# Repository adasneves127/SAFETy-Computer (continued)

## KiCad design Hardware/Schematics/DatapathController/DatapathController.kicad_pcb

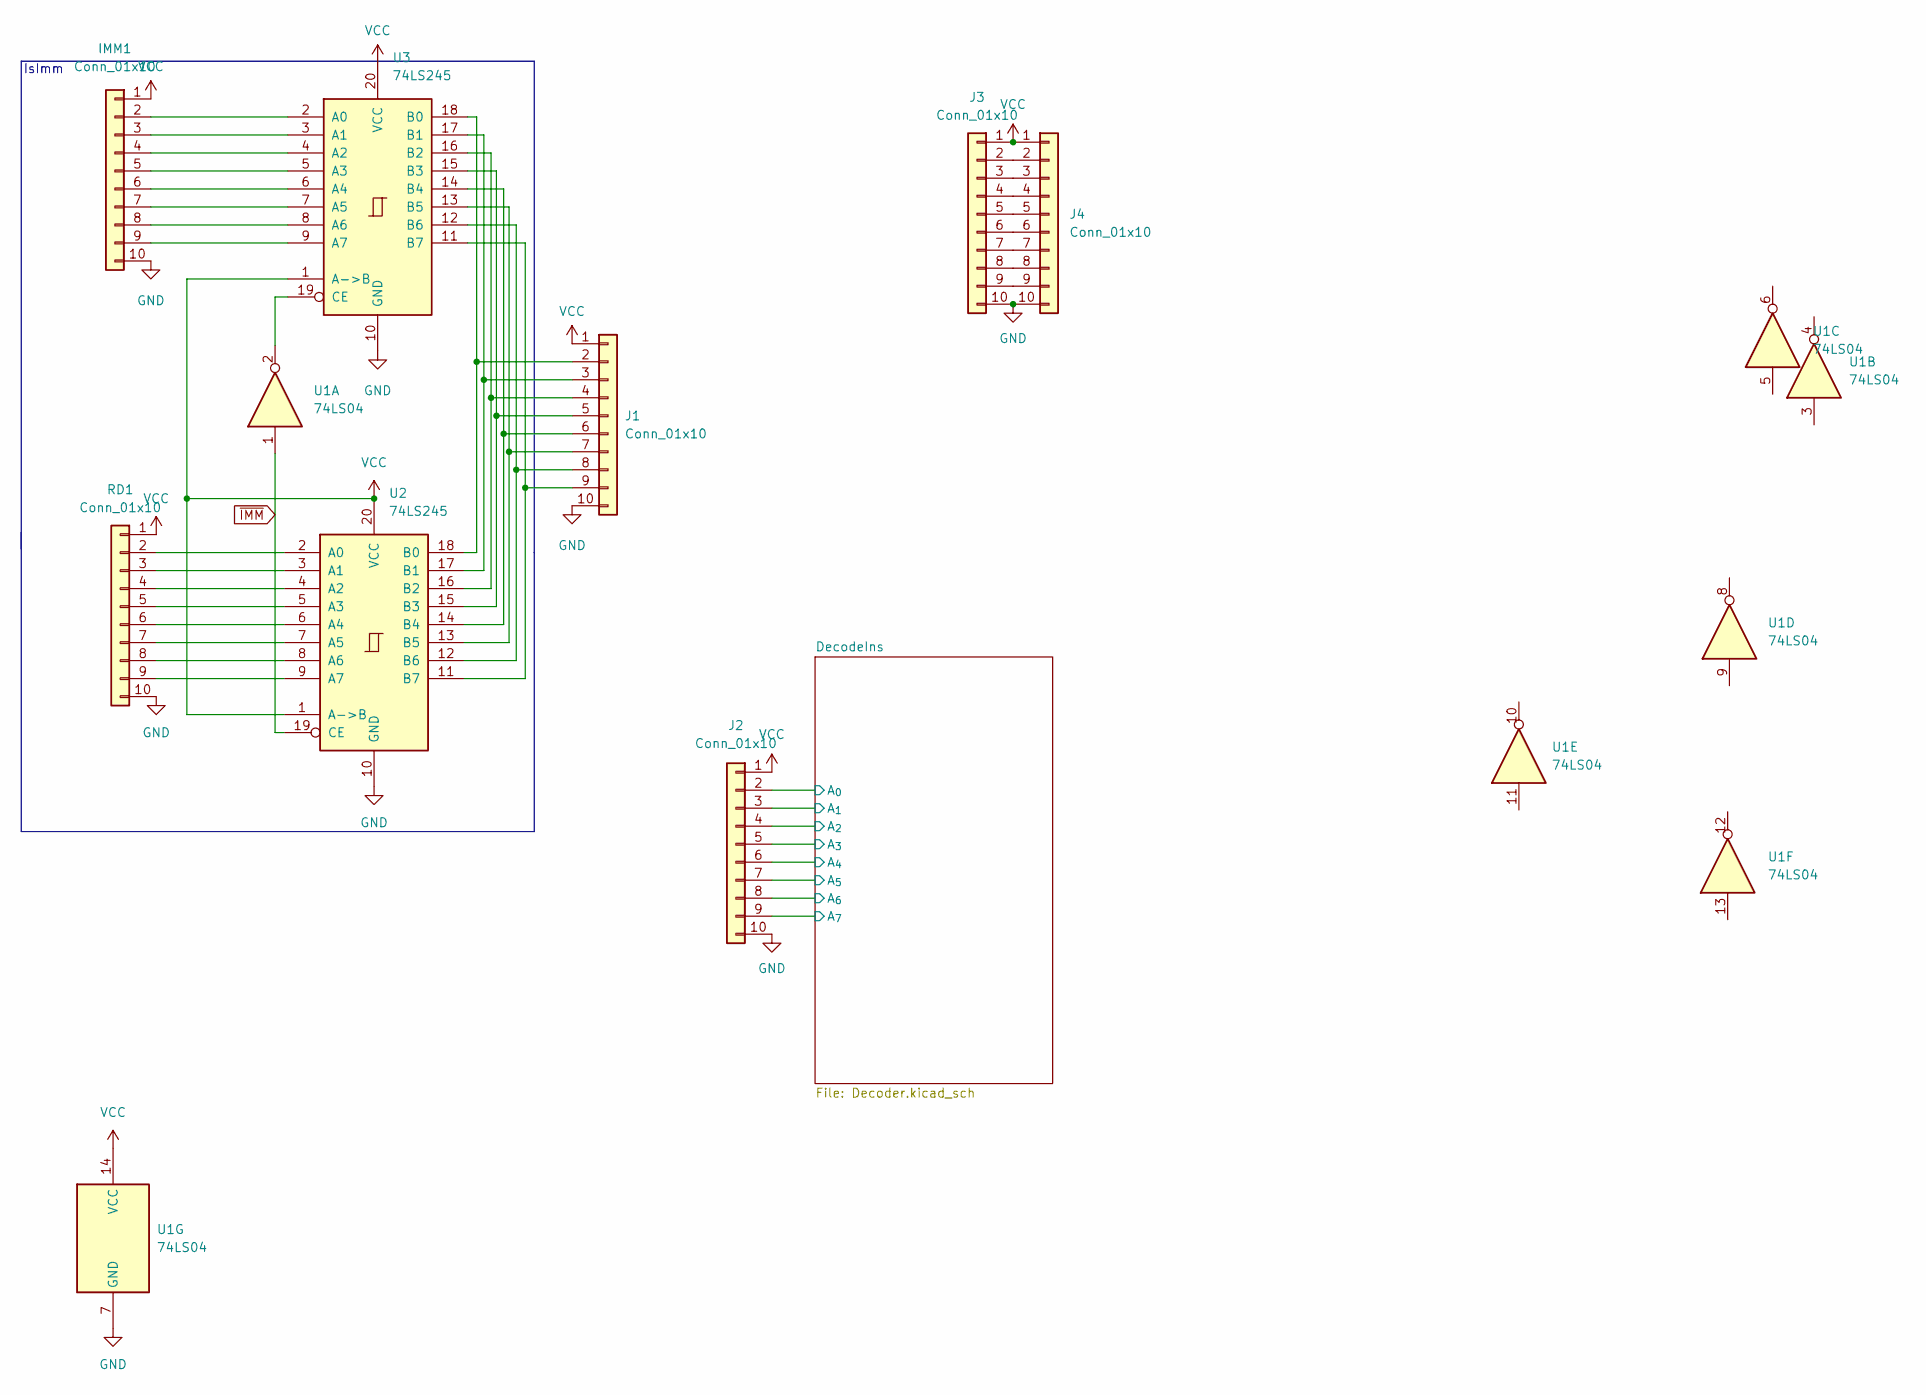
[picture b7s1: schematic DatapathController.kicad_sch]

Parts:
IMM1: Conn_01x10; PinSocket_1x10_P2.54mm_Vertical
J1, J2, J3, J4: Conn_01x10; PinSocket_1x10_P2.54mm_Vertical
RD1: Conn_01x10; PinSocket_1x10_P2.54mm_Vertical
U1: 74LS04; DIP-14_W7.62mm_Socket_LongPads
U2, U3: 74LS245; DIP-20_W7.62mm_Socket_LongPads

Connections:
/DecodeIns/A_{0}: J2.2; also elsewhere on the board
/DecodeIns/A_{1}: J2.3; also elsewhere on the board
/DecodeIns/A_{2}: J2.4; also elsewhere on the board
/DecodeIns/A_{3}: J2.5; also elsewhere on the board
/DecodeIns/A_{4}: J2.6; also elsewhere on the board
/DecodeIns/A_{5}: J2.7; also elsewhere on the board
/DecodeIns/A_{6}: J2.8; also elsewhere on the board
/DecodeIns/A_{7}: J2.9; also elsewhere on the board
GND: IMM1.10, J1.10, J2.10, J3.10, J4.10, RD1.10, U1.7 (GND), U2.10 (GND), U3.10 (GND); also elsewhere on the board
unnamed: IMM1.2, U3.2 (A0)
unnamed: IMM1.3, U3.3 (A1)
unnamed: IMM1.4, U3.4 (A2)
unnamed: IMM1.5, U3.5 (A3)
unnamed: IMM1.6, U3.6 (A4)
unnamed: IMM1.7, U3.7 (A5)
unnamed: IMM1.8, U3.8 (A6)
unnamed: IMM1.9, U3.9 (A7)
unnamed: J1.2, U2.18 (B0), U3.18 (B0)
unnamed: J1.3, U2.17 (B1), U3.17 (B1)
unnamed: J1.4, U2.16 (B2), U3.16 (B2)
unnamed: J1.5, U2.15 (B3), U3.15 (B3)
unnamed: J1.6, U2.14 (B4), U3.14 (B4)
unnamed: J1.7, U2.13 (B5), U3.13 (B5)
unnamed: J1.8, U2.12 (B6), U3.12 (B6)
unnamed: J1.9, U2.11 (B7), U3.11 (B7)
unnamed: J3.2, J4.2
unnamed: J3.3, J4.3
unnamed: J3.4, J4.4
unnamed: J3.5, J4.5
unnamed: J3.6, J4.6
unnamed: J3.7, J4.7
unnamed: J3.8, J4.8
unnamed: J3.9, J4.9
unnamed: RD1.2, U2.2 (A0)
unnamed: RD1.3, U2.3 (A1)
unnamed: RD1.4, U2.4 (A2)
unnamed: RD1.5, U2.5 (A3)
unnamed: RD1.6, U2.6 (A4)
unnamed: RD1.7, U2.7 (A5)
unnamed: RD1.8, U2.8 (A6)
unnamed: RD1.9, U2.9 (A7)
unnamed: U1.2, U3.19 (CE)
VCC: IMM1.1, J1.1, J2.1, J3.1, J4.1, RD1.1, U1.14 (VCC), U2.1 (A->B), U2.20 (VCC), U3.1 (A->B), U3.20 (VCC); also elsewhere on the board
~IMM: U1.1, U2.19 (CE)

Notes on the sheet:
IsImm

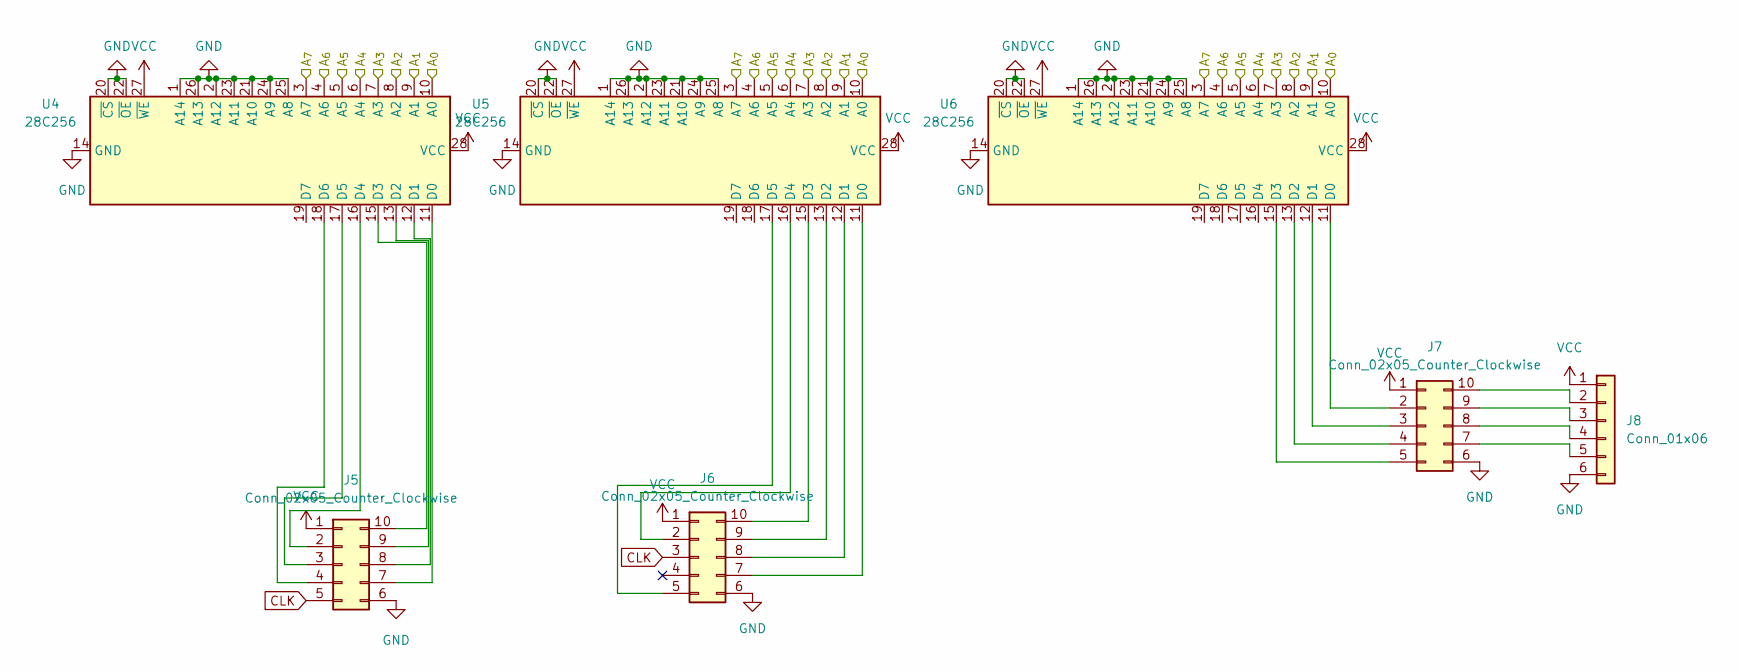
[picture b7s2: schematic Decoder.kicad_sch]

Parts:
J5: Conn_02x05_Counter_Clockwise; PinSocket_2x05_P2.54mm_Vertical
J6, J7: Conn_02x05_Counter_Clockwise; PinHeader_2x05_P2.54mm_Horizontal
J8: Conn_01x06; PinSocket_1x06_P2.54mm_Vertical
U4, U5, U6: 28C256; DIP-28_W15.24mm_Socket_LongPads

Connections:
/DecodeIns/A_{0}: U4.10 (A0), U5.10 (A0), U6.10 (A0); also elsewhere on the board
/DecodeIns/A_{1}: U4.9 (A1), U5.9 (A1), U6.9 (A1); also elsewhere on the board
/DecodeIns/A_{2}: U4.8 (A2), U5.8 (A2), U6.8 (A2); also elsewhere on the board
/DecodeIns/A_{3}: U4.7 (A3), U5.7 (A3), U6.7 (A3); also elsewhere on the board
/DecodeIns/A_{4}: U4.6 (A4), U5.6 (A4), U6.6 (A4); also elsewhere on the board
/DecodeIns/A_{5}: U4.5 (A5), U5.5 (A5), U6.5 (A5); also elsewhere on the board
/DecodeIns/A_{6}: U4.4 (A6), U5.4 (A6), U6.4 (A6); also elsewhere on the board
/DecodeIns/A_{7}: U4.3 (A7), U5.3 (A7), U6.3 (A7); also elsewhere on the board
CLK: J5.5, J6.3
GND: J5.6, J6.6, J7.6, J8.6, U4.1 (A14), U4.2 (A12), U4.14 (GND), U4.20 (~CS), U4.21 (A10), U4.22 (~OE), U4.23 (A11), U4.24 (A9), U4.25 (A8), U4.26 (A13), U5.1 (A14), U5.2 (A12), U5.14 (GND), U5.20 (~CS), U5.21 (A10), U5.22 (~OE), U5.23 (A11), U5.24 (A9), U5.25 (A8), U5.26 (A13), U6.1 (A14), U6.2 (A12), U6.14 (GND), U6.20 (~CS), U6.21 (A10), U6.22 (~OE), U6.23 (A11), U6.24 (A9), U6.25 (A8), U6.26 (A13); also elsewhere on the board
unnamed: J5.2, U4.16 (D4)
unnamed: J5.3, U4.17 (D5)
unnamed: J5.4, U4.18 (D6)
unnamed: J5.7, U4.11 (D0)
unnamed: J5.8, U4.12 (D1)
unnamed: J5.9, U4.13 (D2)
unnamed: J5.10, U4.15 (D3)
unnamed: J6.2, U5.16 (D4)
unnamed: J6.5, U5.17 (D5)
unnamed: J6.7, U5.11 (D0)
unnamed: J6.8, U5.12 (D1)
unnamed: J6.9, U5.13 (D2)
unnamed: J6.10, U5.15 (D3)
unnamed: J7.2, U6.11 (D0)
unnamed: J7.3, U6.12 (D1)
unnamed: J7.4, U6.13 (D2)
unnamed: J7.5, U6.15 (D3)
unnamed: J7.7, J8.5
unnamed: J7.8, J8.4
unnamed: J7.9, J8.3
unnamed: J7.10, J8.2
VCC: J5.1, J6.1, J7.1, J8.1, U4.27 (~WE), U4.28 (VCC), U5.27 (~WE), U5.28 (VCC), U6.27 (~WE), U6.28 (VCC); also elsewhere on the board

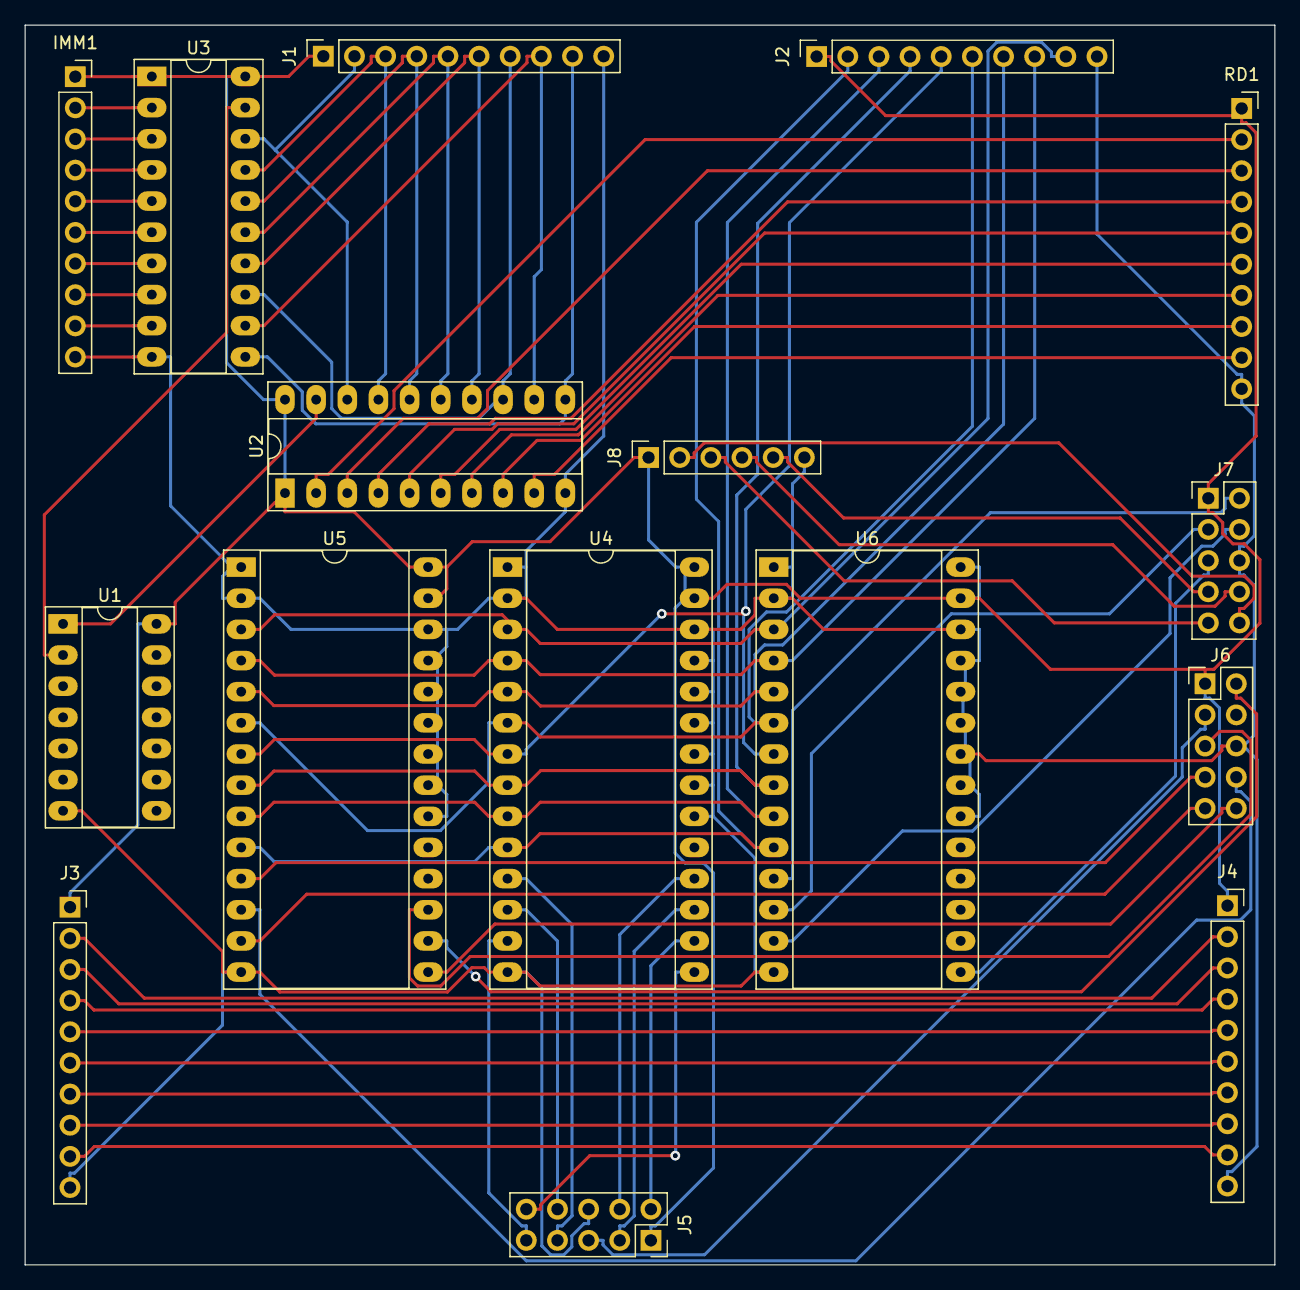
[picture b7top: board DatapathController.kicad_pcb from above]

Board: 2 copper layers, 101.9 x 101.1 mm, 16 parts (0 on the bottom side), 66 nets.

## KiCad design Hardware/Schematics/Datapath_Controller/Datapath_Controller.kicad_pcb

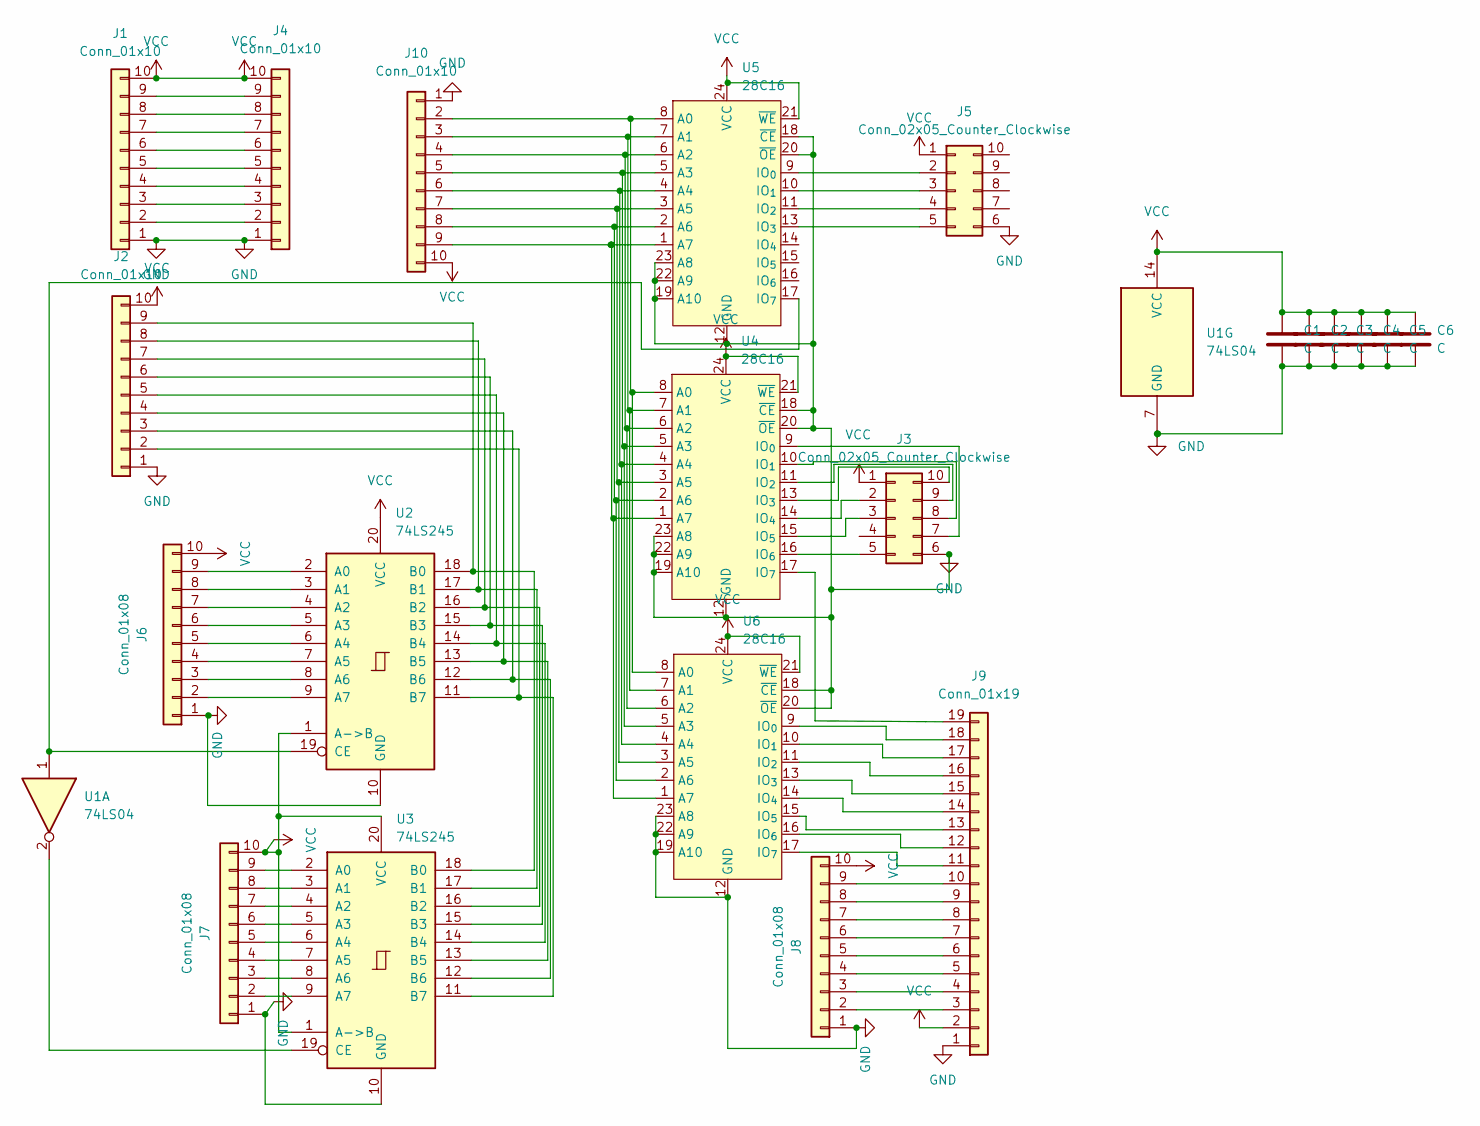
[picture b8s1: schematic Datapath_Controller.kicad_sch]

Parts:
C1, C2, C3, C4, C5, C6: C; C_Rect_L7.0mm_W2.5mm_P5.00mm
J1, J2, J4, J10: Conn_01x10; PinHeader_1x10_P2.54mm_Vertical
J3, J5: Conn_02x05_Counter_Clockwise; PinHeader_2x05_P2.54mm_Vertical
J6, J7, J8: Conn_01x08; PinHeader_1x10_P2.54mm_Vertical
J9: Conn_01x19; PinHeader_1x19_P2.54mm_Vertical
U1: 74LS04; DIP-14_W7.62mm_Socket_LongPads
U2, U3: 74LS245; DIP-20_W7.62mm_Socket_LongPads
U4, U5, U6: 28C16; DIP-24_W15.24mm_Socket_LongPads

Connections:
GND: C1.2, C2.2, C3.2, C4.2, C5.2, C6.2, J1.1, J2.1, J3.6, J4.1, J5.6, J6.1, J7.1, J8.1, J9.1, J10.1, U1.7 (GND), U2.10 (GND), U3.10 (GND), U4.12 (GND), U4.18 (~CE), U4.19 (A10), U4.20 (~OE), U4.22 (A9), U4.23 (A8), U5.12 (GND), U5.18 (~CE), U5.19 (A10), U5.20 (~OE), U5.22 (A9), U5.23 (A8), U6.12 (GND), U6.18 (~CE), U6.19 (A10), U6.20 (~OE), U6.22 (A9), U6.23 (A8)
unnamed: J1.2, J4.2
unnamed: J1.3, J4.3
unnamed: J1.4, J4.4
unnamed: J1.5, J4.5
unnamed: J1.6, J4.6
unnamed: J1.7, J4.7
unnamed: J1.8, J4.8
unnamed: J1.9, J4.9
unnamed: J2.2, U2.11 (B7), U3.11 (B7)
unnamed: J2.3, U2.12 (B6), U3.12 (B6)
unnamed: J2.4, U2.13 (B5), U3.13 (B5)
unnamed: J2.5, U2.14 (B4), U3.14 (B4)
unnamed: J2.6, U2.15 (B3), U3.15 (B3)
unnamed: J2.7, U2.16 (B2), U3.16 (B2)
unnamed: J2.8, U2.17 (B1), U3.17 (B1)
unnamed: J2.9, U2.18 (B0), U3.18 (B0)
unnamed: J3.2, U4.14 (IO_{4})
unnamed: J3.3, U4.15 (IO_{5})
unnamed: J3.5, U4.16 (IO_{6})
unnamed: J3.7, U4.9 (IO_{0})
unnamed: J3.8, U4.10 (IO_{1})
unnamed: J3.9, U4.11 (IO_{2})
unnamed: J3.10, U4.13 (IO_{3})
unnamed: J5.2, U5.9 (IO_{0})
unnamed: J5.3, U5.10 (IO_{1})
unnamed: J5.4, U5.11 (IO_{2})
unnamed: J5.5, U5.13 (IO_{3})
unnamed: J6.2, U2.9 (A7)
unnamed: J6.3, U2.8 (A6)
unnamed: J6.4, U2.7 (A5)
unnamed: J6.5, U2.6 (A4)
unnamed: J6.6, U2.5 (A3)
unnamed: J6.7, U2.4 (A2)
unnamed: J6.8, U2.3 (A1)
unnamed: J6.9, U2.2 (A0)
unnamed: J7.2, U3.9 (A7)
unnamed: J7.3, U3.8 (A6)
unnamed: J7.4, U3.7 (A5)
unnamed: J7.5, U3.6 (A4)
unnamed: J7.6, U3.5 (A3)
unnamed: J7.7, U3.4 (A2)
unnamed: J7.8, U3.3 (A1)
unnamed: J7.9, U3.2 (A0)
unnamed: J8.2, J9.3
unnamed: J8.3, J9.4
unnamed: J8.4, J9.5
unnamed: J8.5, J9.6
unnamed: J8.6, J9.7
unnamed: J8.7, J9.8
unnamed: J8.8, J9.9
unnamed: J8.9, J9.10
unnamed: J9.11, U6.17 (IO_{7})
unnamed: J9.12, U6.16 (IO_{6})
unnamed: J9.13, U6.15 (IO_{5})
unnamed: J9.14, U6.14 (IO_{4})
unnamed: J9.15, U6.13 (IO_{3})
unnamed: J9.16, U6.11 (IO_{2})
unnamed: J9.17, U6.10 (IO_{1})
unnamed: J9.18, U6.9 (IO_{0})
unnamed: J9.19, U4.17 (IO_{7})
unnamed: U1.2, U3.19 (CE)
unnamed: U1.1, U2.19 (CE), U5.17 (IO_{7})
unnamed: J10.9, U4.1 (A7), U5.1 (A7), U6.1 (A7)
unnamed: J10.8, U4.2 (A6), U5.2 (A6), U6.2 (A6)
unnamed: J10.7, U4.3 (A5), U5.3 (A5), U6.3 (A5)
unnamed: J10.6, U4.4 (A4), U5.4 (A4), U6.4 (A4)
unnamed: J10.5, U4.5 (A3), U5.5 (A3), U6.5 (A3)
unnamed: J10.4, U4.6 (A2), U5.6 (A2), U6.6 (A2)
unnamed: J10.3, U4.7 (A1), U5.7 (A1), U6.7 (A1)
unnamed: J10.2, U4.8 (A0), U5.8 (A0), U6.8 (A0)
VCC: C1.1, C2.1, C3.1, C4.1, C5.1, C6.1, J1.10, J2.10, J3.1, J4.10, J5.1, J6.10, J7.10, J8.10, J9.2, J10.10, U1.14 (VCC), U2.1 (A->B), U2.20 (VCC), U3.1 (A->B), U3.20 (VCC), U4.21 (~WE), U4.24 (VCC), U5.24 (VCC), U6.21 (~WE), U6.24 (VCC)

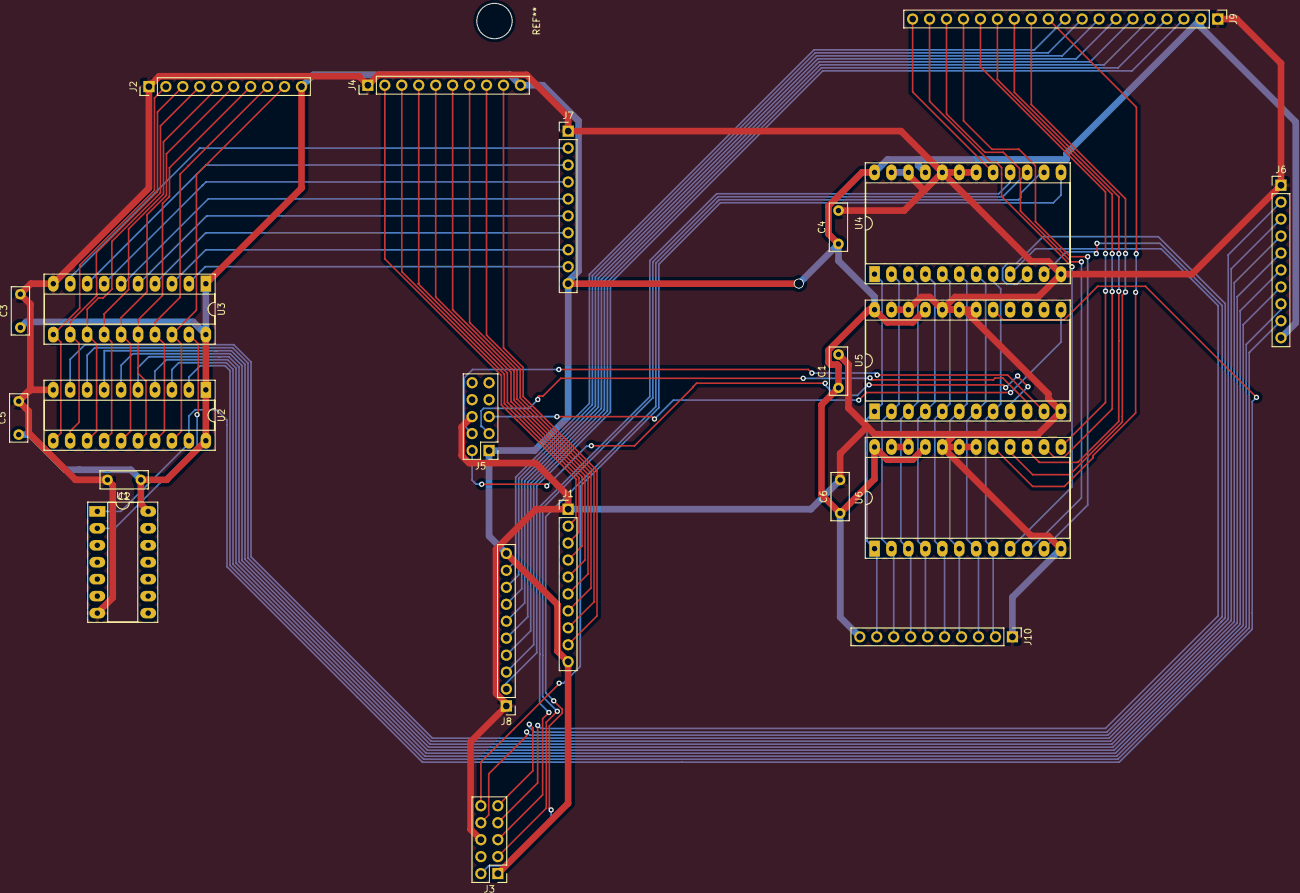
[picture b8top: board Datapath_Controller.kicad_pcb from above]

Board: 2 copper layers, 22 parts (0 on the bottom side), 72 nets.

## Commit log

2022-10-17 Interim
2022-10-17 Added ALU Schematics
2022-10-17 Added ALU
2022-10-31 hrau
2022-11-17 Finished Registers, Started ALU
2022-11-17 Nightly Commit
2022-11-28 Fixed Lockfile and added to gitignore
2022-11-30 Started Another Rewrite of Assembler
2022-12-01 Updated SAFETy Instructions
2022-12-01 Started Calling
2022-12-01 Created cpp Simulator basis
2022-12-01 Updated Gitignore
2022-12-01 PrePreProcessed
2022-12-01 Added Component Files
2022-12-01 Before Fucks with char*
2022-12-02 Night Time
2022-12-05 More Asm work - removed macros
2022-12-07 Interim Pt.2
2022-12-09 Updated Monitor
2022-12-09 Implementing Basic Instructions
2022-12-09 Added Load Instructions
2022-12-09 Tested Loads
2022-12-09 Added More Memory Functions
2022-12-11 Added 'add' and 'sub' inst
2022-12-11 NAND, PUSHm STORE, and CMP added
2022-12-12 Updated Monitor to be intuitive with `Inspect`
2022-12-12 Cleaned up some formatting.
2022-12-16 Updated Makefile
    Fixes Issue #6.
2022-12-21 All integral instructions implemented!
2022-12-21 implemented System Stack
2023-01-02 Created a mostly working Assembler
2023-01-02 Assembler Call Implemented
2023-01-02 Fixed Lockfile Ignore
2023-01-03 Delete Hardware/Schematics/ALU directory
    Resolves a conflict
    These schematics have been superseded by the AlexSchems branch.
2023-01-04 Added Keyboard Conversion bin
2023-01-10 Added Return from Call
2023-01-10 Created Config File
2023-01-10 Renamed Working Assembler
2023-01-10 Cleaned Up
2023-01-12 ALU Design Finished
2023-01-12 Added Datapath Controller
2023-01-14 Finished Datapath Controller
2023-01-26 Updated Simultor (Removed Tools.cpp)
2023-01-26 Cleaned up compiler
2023-01-27 Removed Stuck Lock
2023-01-30 Added RFC Instruction
2023-02-08 Removed old syntax highlighting
2023-03-02 Updated Schematics
2023-03-12 Updated and Created more Schems
2023-03-16 Interim Commit
2023-03-16 removed Schematics
2023-03-16 Updated All Schematics to be up-to-date
2023-03-30 Restarting Simulator
2023-04-02 Boards Done
